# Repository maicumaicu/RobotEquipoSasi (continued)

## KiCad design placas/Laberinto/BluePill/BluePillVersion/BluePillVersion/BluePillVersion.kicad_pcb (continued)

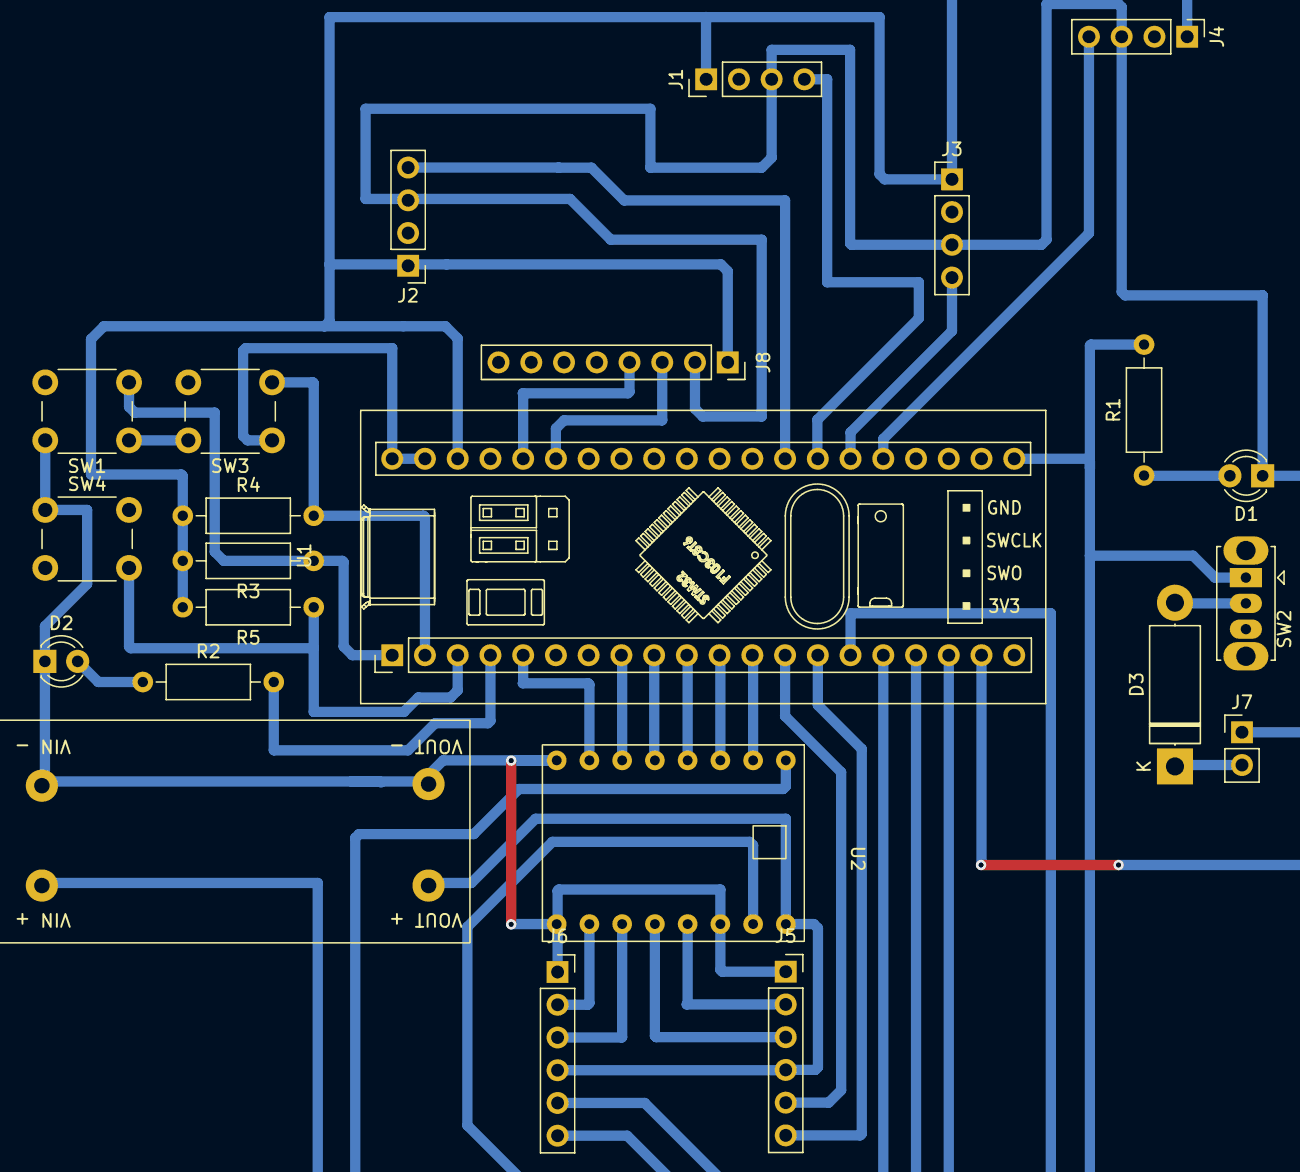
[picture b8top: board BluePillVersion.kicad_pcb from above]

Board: 2 copper layers, 23 parts (0 on the bottom side), 34 nets.

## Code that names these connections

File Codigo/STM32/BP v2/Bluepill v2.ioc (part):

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Mcu.Name=STM32F103C(8-B)Tx
Mcu.Package=LQFP48
Mcu.UserName=STM32F103C8Tx
PA0-WKUP.GPIOParameters=GPIO_Label
PA0-WKUP.GPIO_Label=CNY70
PA0-WKUP.Signal=ADCx_IN0
PA1.GPIOParameters=GPIO_Label
PA1.GPIO_Label=SHARP_D
PA1.Signal=ADCx_IN1
PA12.GPIOParameters=GPIO_Label
PA12.GPIO_Label=BIN2
PA12.Signal=GPIO_Output
PA13.Mode=Serial_Wire
PA13.Signal=SYS_JTMS-SWDIO
PA14.Mode=Serial_Wire
PA14.Signal=SYS_JTCK-SWCLK
PA15.GPIOParameters=GPIO_Label
PA15.GPIO_Label=BIN1
PA15.Signal=GPIO_Output
PA2.GPIOParameters=GPIO_Label
PA2.GPIO_Label=SHARP_C
PA2.Signal=ADCx_IN2
PA3.GPIOParameters=GPIO_Label
PA3.GPIO_Label=SHARP_I
PA3.Signal=ADCx_IN3
PA6.Signal=S_TIM3_CH1
PA7.Signal=S_TIM3_CH2
PA8.Signal=S_TIM1_CH1
PA9.Signal=S_TIM1_CH2
PB10.Mode=Asynchronous
PB10.Signal=USART3_TX
PB11.Mode=Asynchronous
PB11.Signal=USART3_RX
PB12.GPIOParameters=GPIO_PuPd,GPIO_Label
PB12.GPIO_Label=BTN1
PB12.GPIO_PuPd=GPIO_PULLUP
PB12.Signal=GPIO_Input
PB13.GPIOParameters=GPIO_PuPd,GPIO_Label
PB13.GPIO_Label=BTN2
PB13.GPIO_PuPd=GPIO_PULLUP
PB13.Signal=GPIO_Input
PB14.GPIOParameters=GPIO_PuPd,GPIO_Label
PB14.GPIO_Label=BTN3
PB14.GPIO_PuPd=GPIO_PULLUP
PB14.Signal=GPIO_Input
PB15.GPIOParameters=GPIO_Label
PB15.GPIO_Label=LED
PB15.Signal=GPIO_Output
PB3.GPIOParameters=GPIO_Label
PB3.GPIO_Label=STBY
PB3.Signal=GPIO_Output
PB4.GPIOParameters=GPIO_Label
PB4.GPIO_Label=AIN1
PB4.Signal=GPIO_Output
PB5.GPIOParameters=GPIO_Label
PB5.GPIO_Label=AIN2
PB5.Signal=GPIO_Output
PB6.Mode=I2C
PB6.Signal=I2C1_SCL
PB7.Mode=I2C
PB7.Signal=I2C1_SDA
PB8.Signal=S_TIM4_CH3
PB9.Signal=S_TIM4_CH4
PC13-TAMPER-RTC.Signal=GPIO_Output
PD0-OSC_IN.Mode=HSE-External-Oscillator
PD0-OSC_IN.Signal=RCC_OSC_IN
PD1-OSC_OUT.Mode=HSE-External-Oscillator
PD1-OSC_OUT.Signal=RCC_OSC_OUT
RCC.SYSCLKFreq_VALUE=72000000
RCC.SYSCLKSource=RCC_SYSCLKSOURCE_PLLCLK
board=custom

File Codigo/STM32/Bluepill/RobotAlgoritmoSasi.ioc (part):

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Mcu.Name=STM32F103C(8-B)Tx
Mcu.Package=LQFP48
Mcu.UserName=STM32F103C8Tx
PA0-WKUP.GPIOParameters=GPIO_Label
PA0-WKUP.GPIO_Label=CNY70
PA0-WKUP.Signal=ADCx_IN0
PA1.GPIOParameters=GPIO_Label
PA1.GPIO_Label=SHARP_D
PA1.Signal=ADCx_IN1
PA10.Mode=Asynchronous
PA10.Signal=USART1_RX
PA11.GPIOParameters=GPIO_Label
PA11.GPIO_Label=BIN2
PA11.Signal=GPIO_Output
PA12.GPIOParameters=GPIO_Label
PA12.GPIO_Label=BIN1
PA12.Signal=GPIO_Output
PA13.Mode=Serial_Wire
PA13.Signal=SYS_JTMS-SWDIO
PA14.Mode=Serial_Wire
PA14.Signal=SYS_JTCK-SWCLK
PA15.GPIOParameters=GPIO_Label
PA15.GPIO_Label=STBY
PA15.Signal=GPIO_Output
PA2.GPIOParameters=GPIO_Label
PA2.GPIO_Label=SHARP_C
PA2.Signal=ADCx_IN2
PA3.GPIOParameters=GPIO_Label
PA3.GPIO_Label=SHARP_I
PA3.Signal=ADCx_IN3
PA6.GPIOParameters=GPIO_Label
PA6.GPIO_Label=MB1
PA6.Signal=S_TIM3_CH1
PA7.GPIOParameters=GPIO_Label
PA7.GPIO_Label=MB2
PA7.Signal=S_TIM3_CH2
PA9.Mode=Asynchronous
PA9.Signal=USART1_TX
PB10.GPIOParameters=GPIO_Label
PB10.GPIO_Label=PWMA
PB10.Signal=S_TIM2_CH3
PB11.GPIOParameters=GPIO_Label
PB11.GPIO_Label=PWMB
PB11.Signal=S_TIM2_CH4
PB12.GPIOParameters=GPIO_Label
PB12.GPIO_Label=BTN1
PB12.Signal=GPIO_Input
PB13.GPIOParameters=GPIO_Label
PB13.GPIO_Label=BTN2
PB13.Signal=GPIO_Input
PB14.GPIOParameters=GPIO_Label
PB14.GPIO_Label=BTN3
PB14.Signal=GPIO_Input
PB15.GPIOParameters=GPIO_Label
PB15.GPIO_Label=LED
PB15.Signal=GPIO_Output
PB3.GPIOParameters=GPIO_Label
PB3.GPIO_Label=AIN1
PB3.Signal=GPIO_Output
PB4.GPIOParameters=GPIO_Label
PB4.GPIO_Label=AIN2
PB4.Signal=GPIO_Output
PB6.GPIOParameters=GPIO_Speed,GPIO_PuPd,GPIO_Label,GPIO_Mode
PB6.GPIO_Label=MA2
PB6.GPIO_Mode=GPIO_MODE_INPUT
PB6.GPIO_PuPd=GPIO_NOPULL
PB6.GPIO_Speed=N/A
PB6.Signal=S_TIM4_CH1
PB7.GPIOParameters=GPIO_Label
PB7.GPIO_Label=MA1
PB7.Signal=S_TIM4_CH2
PC13-TAMPER-RTC.Signal=GPIO_Output
PD0-OSC_IN.Mode=HSE-External-Oscillator
PD0-OSC_IN.Signal=RCC_OSC_IN
PD1-OSC_OUT.Mode=HSE-External-Oscillator
PD1-OSC_OUT.Signal=RCC_OSC_OUT
RCC.SYSCLKFreq_VALUE=72000000
RCC.SYSCLKSource=RCC_SYSCLKSOURCE_PLLCLK
board=custom

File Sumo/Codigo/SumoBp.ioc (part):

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Mcu.Name=STM32F103C(8-B)Tx
Mcu.Package=LQFP48
Mcu.UserName=STM32F103C8Tx
PA0-WKUP.GPIOParameters=GPIO_Label
PA0-WKUP.GPIO_Label=P1
PA0-WKUP.Signal=ADCx_IN0
PA1.GPIOParameters=GPIO_Label
PA1.GPIO_Label=P2
PA1.Signal=ADCx_IN1
PA10.GPIOParameters=GPIO_Label
PA10.GPIO_Label=S1
PA10.Signal=GPIO_Input
PA11.GPIOParameters=GPIO_Label
PA11.GPIO_Label=S2
PA11.Signal=GPIO_Input
PA13.Mode=Serial_Wire
PA13.Signal=SYS_JTMS-SWDIO
PA14.Mode=Serial_Wire
PA14.Signal=SYS_JTCK-SWCLK
PA15.GPIOParameters=GPIO_Label
PA15.GPIO_Label=B4
PA15.Signal=GPIO_Input
PA2.GPIOParameters=GPIO_Label
PA2.GPIO_Label=P3
PA2.Signal=ADCx_IN2
PA3.GPIOParameters=GPIO_Label
PA3.GPIO_Label=P4
PA3.Signal=ADCx_IN3
PA4.GPIOParameters=GPIO_Label
PA4.GPIO_Label=P5
PA4.Signal=ADCx_IN4
PA5.GPIOParameters=GPIO_Label
PA5.GPIO_Label=EN1
PA5.Signal=GPIO_Output
PA6.Signal=S_TIM3_CH1
PA7.GPIOParameters=GPIO_Label
PA7.GPIO_Label=INB1
PA7.Signal=GPIO_Output
PA8.Signal=GPIO_Input
PA9.Signal=GPIO_Input
PB0.GPIOParameters=GPIO_Label
PB0.GPIO_Label=INA2
PB0.Signal=GPIO_Output
PB1.Signal=S_TIM3_CH4
PB10.GPIOParameters=GPIO_Label
PB10.GPIO_Label=INB2
PB10.Signal=GPIO_Output
PB11.GPIOParameters=GPIO_Label
PB11.GPIO_Label=INA1
PB11.Signal=GPIO_Output
PB12.Signal=GPIO_Input
PB13.Signal=GPIO_Input
PB14.Signal=GPIO_Input
PB15.Signal=GPIO_Input
PB3.GPIOParameters=GPIO_Label
PB3.GPIO_Label=B3
PB3.Signal=GPIO_Input
PB4.GPIOParameters=GPIO_Label
PB4.GPIO_Label=B2
PB4.Signal=GPIO_Input
PB5.GPIOParameters=GPIO_Label
PB5.GPIO_Label=B1
PB5.Signal=GPIO_Input
PB6.GPIOParameters=GPIO_Label
PB6.GPIO_Label=L1
PB6.Signal=GPIO_Output
PB7.GPIOParameters=GPIO_Label
PB7.GPIO_Label=L2
PB7.Signal=GPIO_Output
PB8.GPIOParameters=GPIO_Label
PB8.GPIO_Label=L3
PB8.Signal=GPIO_Output
PB9.GPIOParameters=GPIO_Label
PB9.GPIO_Label=L4
PB9.Signal=GPIO_Output
PC13-TAMPER-RTC.Signal=GPIO_Output
PD0-OSC_IN.Mode=HSE-External-Oscillator
PD0-OSC_IN.Signal=RCC_OSC_IN
PD1-OSC_OUT.Mode=HSE-External-Oscillator
PD1-OSC_OUT.Signal=RCC_OSC_OUT
RCC.SYSCLKFreq_VALUE=72000000
RCC.SYSCLKSource=RCC_SYSCLKSOURCE_PLLCLK
board=custom

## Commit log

2022-06-19 Termino Algoritmo mapeo con dfs
2022-06-20 Arreglo bug de paredes
    convertia paredes 1 en paredes 2 haciendo que se trabe
2022-06-21 Armo el eliminador de caminos y me preparo para agregar el EEPROM
2022-06-28 armando el sistema de carrera
2022-06-29 armo la maquina de estados del robot real
2022-06-29 sigo laburando
2022-07-09 subo prueba
2022-07-13 subo mierdsa por las dudas
2022-07-14 subo la mierda que hice y se borro
2022-07-14 subo contenido
2022-07-14 hola
2022-07-25 sgfdfg
2022-07-28 kicad update
2022-08-03 cualquier cosa. jaja
    ..
2022-08-03 sfgdh
2022-08-14 sdcdsc
2022-08-16 4545
2022-08-17 23542
2022-08-17 dsfdf
2022-08-19 4155456
2022-08-21 fdgkl
2022-08-31 eefef
2022-09-08 kfd[lbg[ldf
2022-09-17 fghg
2022-09-28 4521
2022-09-30 sjdgkdfjgk
2022-10-03 fghjgf
2022-10-06 gghh
2022-10-07 sdokfo
2022-10-07 cvhgfh
2022-10-07 hjkjh
2022-10-08 lkdssdfl'sfl
2022-10-10 fgutu
2022-10-10 fgdgf
2022-10-11 gdfgfg
2022-10-29 ygjhghj
2022-11-08 dufg9uf9
2022-11-18 fdgfdg
2022-11-30 vhhj
2023-05-26 fhfhfhg
2023-06-01 fgfgh
2023-06-04 fsdf
2023-08-02 CAMBIOS
2023-08-03 placa sensores
2023-09-12 .....1234
2023-09-19 ghghg
2023-10-16 gggg
2023-10-16 gfgf
2023-11-10 fngvfng
2024-02-02 ujfjgh
